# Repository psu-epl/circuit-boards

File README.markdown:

Circuit Board Building
======================

The [L.I.D.](http://pdx.edu/interconnected) had the ablity to let students build
high quility prototype two layer circuit boards in a short amount of time. We
have two PCB routers to accomplish this task:

### [LPKF s63](LPKF)

### [AccruateCNC A406](A406)

and a electroplating tank for plating Vias:

### [LPKF MiniContac RS](Electroplating_Tank)

# Make A Board Using Eagle

If you are using Eagle to make a board, use our handy CAM and DRU files to
check your board before you route, and to make gerbers.

### [Download Zip File](https://github.com/psu-epl/circuit-boards/archive/master.zip)

Inside the zip there is a folder called `eagle`. That has the cam and dru files
for this lab.

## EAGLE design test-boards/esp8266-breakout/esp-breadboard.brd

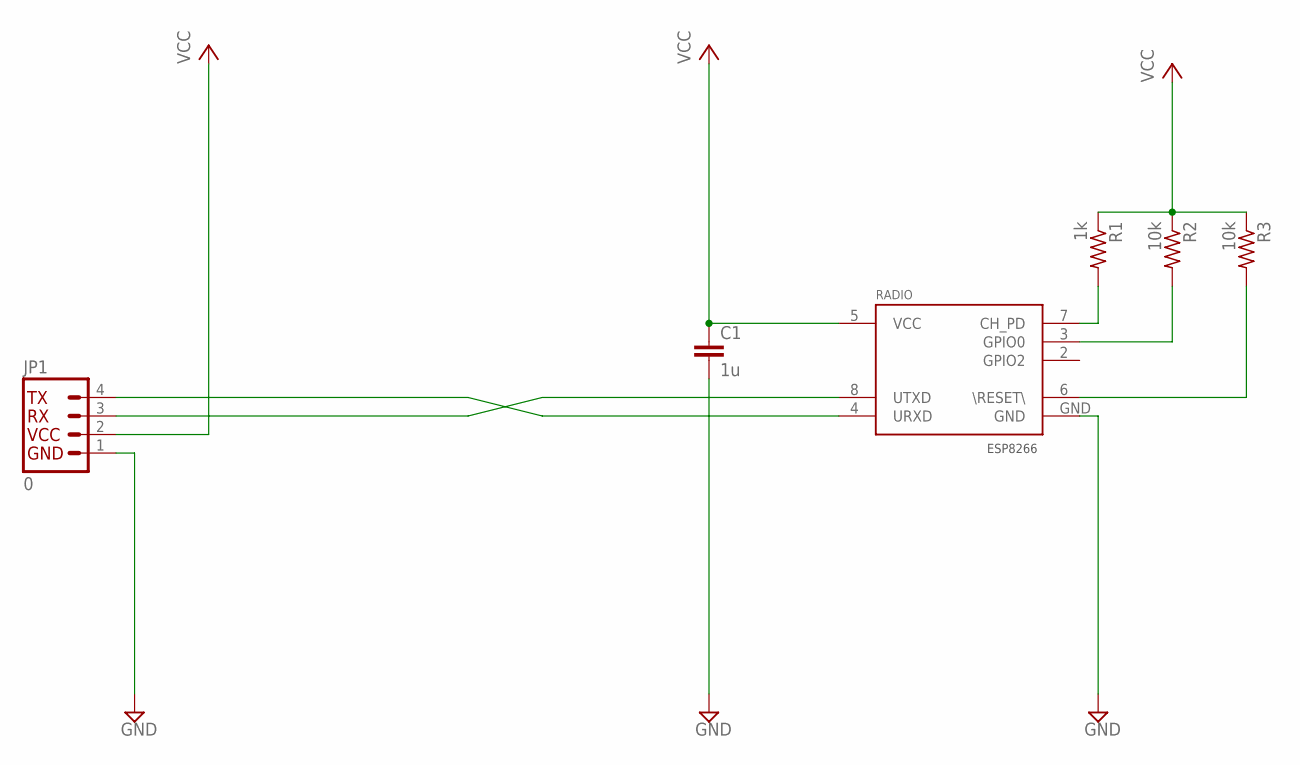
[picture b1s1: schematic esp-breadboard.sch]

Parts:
C1: 1u; C0805
JP1: 0; 1X04_NO_SILK
R1: 1k; R0805
R2, R3: 10k; R0805
RADIO: ESP8266; ESP8266-01

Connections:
ESPRX: JP1.4, RADIO.4 (URXD)
ESPTX: JP1.3, RADIO.8 (UTXD)
GND: C1.2, JP1.1, RADIO.GND
unnamed: R2.2, RADIO.3 (GPIO0)
unnamed: R1.2, RADIO.7 (CH_PD)
unnamed: R3.2, RADIO.6 (\RESET\)
VCC: C1.1, JP1.2, R1.1, R2.1, R3.1, RADIO.5 (VCC)

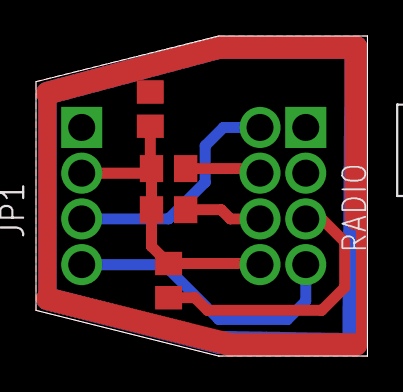
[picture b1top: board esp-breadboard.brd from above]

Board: 2 copper layers, 18.4 x 17.8 mm, 6 parts (0 on the bottom side), 7 nets.

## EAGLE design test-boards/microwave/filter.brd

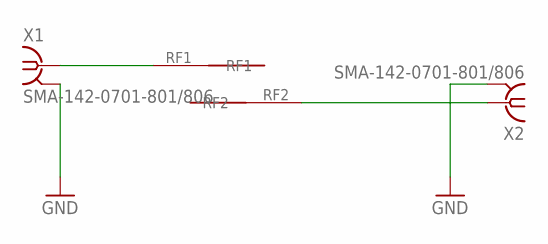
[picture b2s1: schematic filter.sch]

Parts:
U$1: FILTER; RF
X1, X2: SMA-142-0701-801/806; J502-ND-142-0701-801/806

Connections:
GND: X1.G@1 (2), X1.G@2 (2), X1.G@3 (2), X1.G@4 (2), X2.G@1 (2), X2.G@2 (2), X2.G@3 (2), X2.G@4 (2)
SIG1: U$1.RF1, X1.1
SIG2: U$1.RF2, X2.1

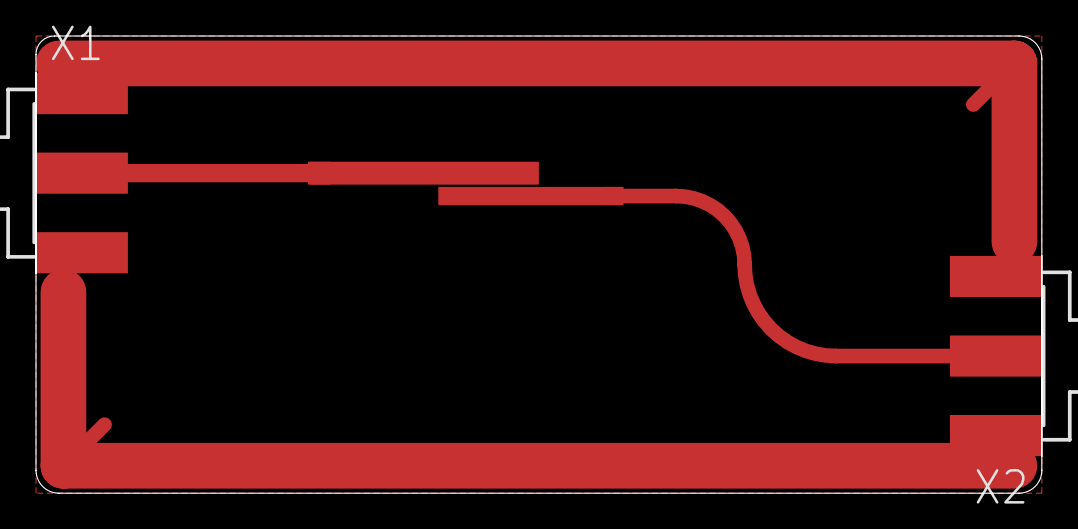
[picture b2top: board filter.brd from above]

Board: 2 copper layers, 55.9 x 25.4 mm, 3 parts (0 on the bottom side), 3 nets.

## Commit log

2013-03-04 cam and dru files for the LPKF
2013-03-05 making eagle file folder
2013-03-10 Added CAM job for single sided boards with traces on bottom layer.
2015-03-04 RF-like test board for routers
2015-03-04 cleaning makefile for gerbers and eagle cruft
2015-03-04 default display in eagle for RF board
2015-03-06 Defaults from LPKF
2015-03-06 LPKF readme
2015-03-06 Use our cam file name defaults
2015-05-12 include stencils for solder mask and solder paste in CAM jobs
2015-06-19 esp8266 library part
2015-06-19 ESP Breakout schematic
2015-06-19 first breadboard
2015-06-19 ESP makefile
2015-06-19 cleanup to esp breadboard breakout
2015-07-08 ESP8266: misplaced RX and GPIO pin, switch around and resize board
2015-08-18 Move to Gerber_24 in 2-layer cam job
2015-08-18 move to Gerber 24 for all cam files
2016-01-09 Soldering Workshop
2016-01-21 AMP
    Modified stereo jack vias
2016-02-18 Update
    Moved soldering workshop
2017-04-14 added bit inventory list
